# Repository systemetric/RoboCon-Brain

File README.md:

# RoboCon-Brain
Custom hardware and firmware for the RoboCon Brain, with PCB designs, embedded software and supporting files. Generations are documented through dedicated branches.

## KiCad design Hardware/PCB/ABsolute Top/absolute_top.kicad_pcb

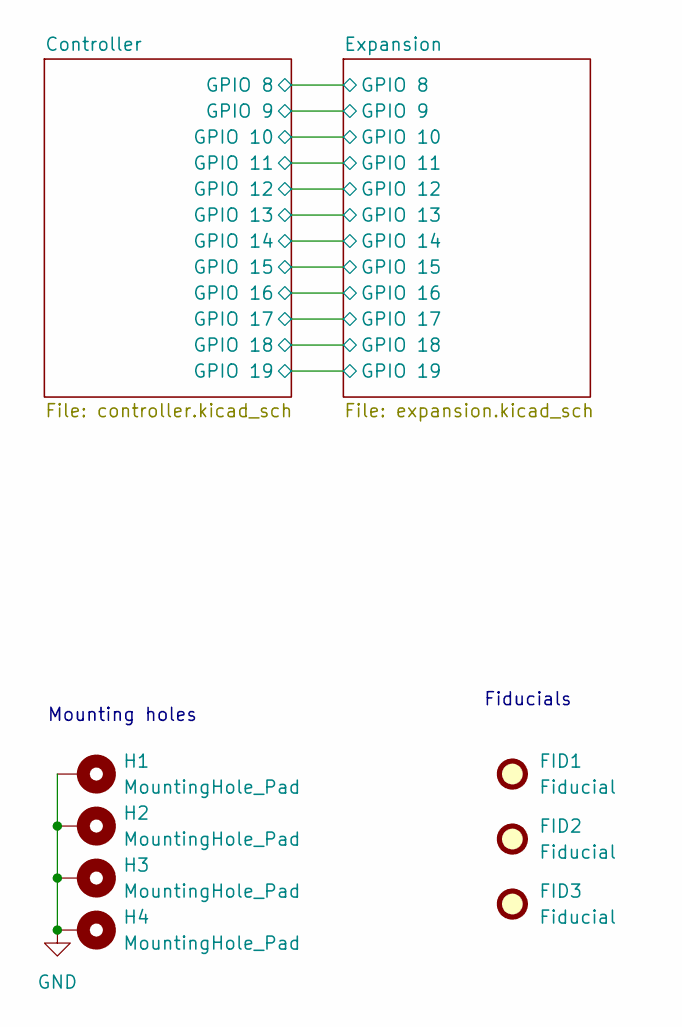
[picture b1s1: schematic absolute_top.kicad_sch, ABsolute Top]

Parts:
FID1, FID2, FID3: Fiducial; Fiducial_1mm_Mask2mm
H1, H2, H3, H4: MountingHole_Pad; MountingHole_3.2mm_M3_Pad_Via

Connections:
GND: H1.1 (1_1), H2.1 (1_1), H3.1 (1_1), H4.1 (1_1); also elsewhere on the board

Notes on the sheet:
Fiducials
Mounting holes

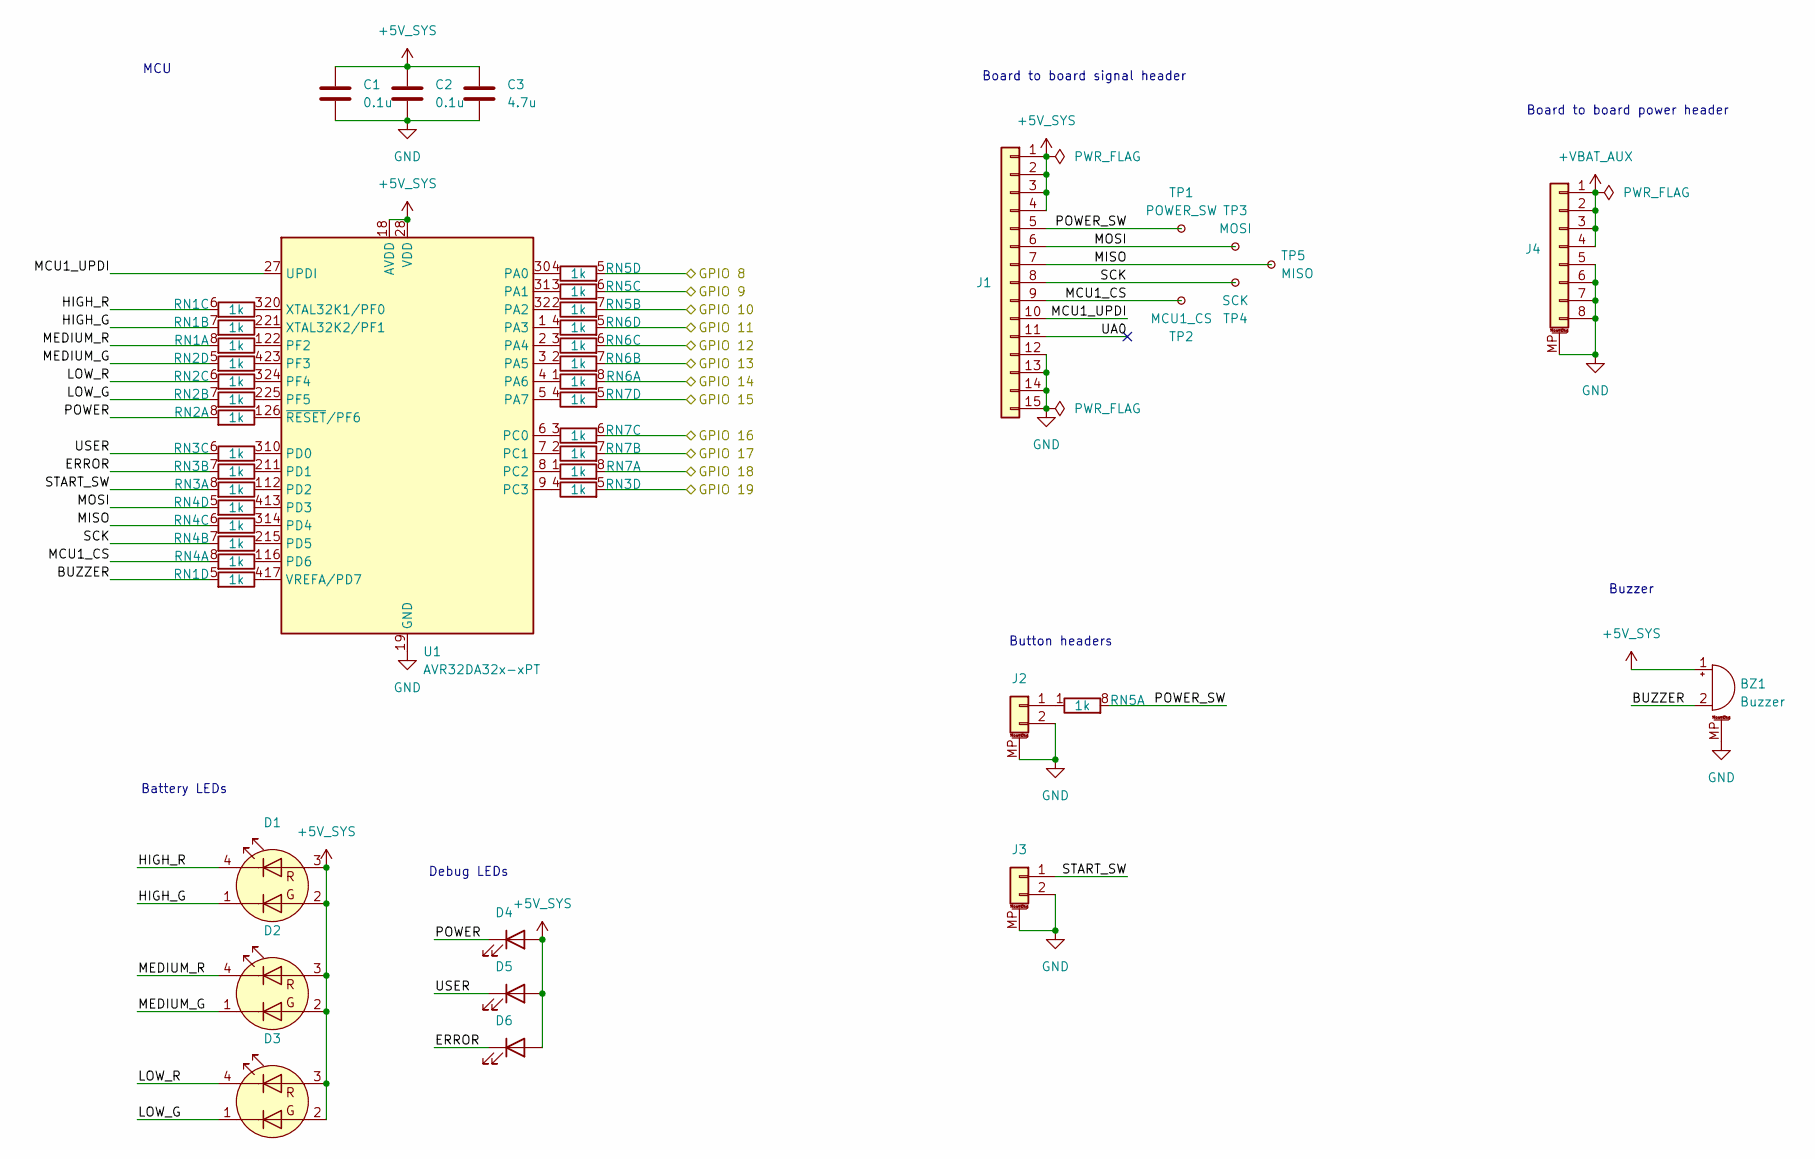
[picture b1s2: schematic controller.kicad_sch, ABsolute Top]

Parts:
BZ1: Buzzer; MagneticBuzzer_CUI_CMT-8504-100-SMT
C1, C2: 0.1u; C_0603_1608Metric
C3: 4.7u; C_0603_1608Metric
D1, D2, D3: LTST-C235KGKRKT; LED_LiteOn_LTST-C235; MPN LTST-C235KGKRKT
D4: LTST-C230KGKT; LED_LiteOn_LTST-C230; MPN LTST-C230KGKT
D5: LTST-C230TBKT; LED_LiteOn_LTST-C230; MPN LTST-C230TBKT
D6: LTST-C230KRKT; LED_LiteOn_LTST-C230; MPN LTST-C230KRKT
J1: Conn_01x15; PinSocket_1x15_P1.00mm_Vertical_SMD_Pin1Left
J2, J3: Conn_01x02_MountingPin; JST_PH_S2B-PH-SM4-TB_1x02-1MP_P2.00mm_Horizontal
J4: Conn_01x08_MountingPin; JST_PH_B8B-PH-SM4-TB_1x08-1MP_P2.00mm_Vertical
RN1, RN2, RN3, RN4, RN5, RN6, RN7: 1k; R_Array_Convex_4x0603
TP1: POWER_SW; TestPoint_Pad_D1.5mm
TP2: MCU1_CS; TestPoint_Pad_D1.5mm
TP3: MOSI; TestPoint_Pad_D1.5mm
TP4: SCK; TestPoint_Pad_D1.5mm
TP5: MISO; TestPoint_Pad_D1.5mm
U1: AVR32DA32x-xPT; TQFP-32_7x7mm_P0.8mm

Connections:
+5V_SYS: BZ1.1 (+), C1.1, C2.1, C3.1, D1.2 (A2), D1.3 (A1), D2.2 (A2), D2.3 (A1), D3.2 (A2), D3.3 (A1), D4.2 (A), D5.2 (A), D6.2 (A), J1.1, J1.2, J1.3, J1.4, U1.18 (AVDD), U1.28 (VDD)
+VBAT_AUX: J4.1, J4.2, J4.3, J4.4
/Controller/BUZZER: BZ1.2 (-), RN1.5 (R4.2)
/Controller/ERROR: D6.1 (K), RN3.7 (R2.2)
/Controller/GPIO 8: RN5.5 (R4.2); also elsewhere on the board
/Controller/GPIO 9: RN5.6 (R3.2); also elsewhere on the board
/Controller/GPIO 10: RN5.7 (R2.2); also elsewhere on the board
/Controller/GPIO 11: RN6.5 (R4.2); also elsewhere on the board
/Controller/GPIO 12: RN6.6 (R3.2); also elsewhere on the board
/Controller/GPIO 13: RN6.7 (R2.2); also elsewhere on the board
/Controller/GPIO 14: RN6.8 (R1.2); also elsewhere on the board
/Controller/GPIO 15: RN7.5 (R4.2); also elsewhere on the board
/Controller/GPIO 16: RN7.6 (R3.2); also elsewhere on the board
/Controller/GPIO 17: RN7.7 (R2.2); also elsewhere on the board
/Controller/GPIO 18: RN7.8 (R1.2); also elsewhere on the board
/Controller/GPIO 19: RN3.5 (R4.2); also elsewhere on the board
/Controller/HIGH_G: D1.1 (K2), RN1.7 (R2.2)
/Controller/HIGH_R: D1.4 (K1), RN1.6 (R3.2)
/Controller/LOW_G: D3.1 (K2), RN2.7 (R2.2)
/Controller/LOW_R: D3.4 (K1), RN2.6 (R3.2)
/Controller/MCU1_CS: J1.9, RN4.8 (R1.2), TP2.1 (1_1)
/Controller/MCU1_UPDI: J1.10, U1.27 (UPDI)
/Controller/MEDIUM_G: D2.1 (K2), RN2.5 (R4.2)
/Controller/MEDIUM_R: D2.4 (K1), RN1.8 (R1.2)
/Controller/MISO: J1.7, RN4.6 (R3.2), TP5.1 (1_1)
/Controller/MOSI: J1.6, RN4.5 (R4.2), TP3.1 (1_1)
/Controller/POWER: D4.1 (K), RN2.8 (R1.2)
/Controller/POWER_SW: J1.5, RN5.8 (R1.2), TP1.1 (1_1)
/Controller/SCK: J1.8, RN4.7 (R2.2), TP4.1 (1_1)
/Controller/START_SW: J3.1, RN3.8 (R1.2)
/Controller/UA0: J1.11
/Controller/USER: D5.1 (K), RN3.6 (R3.2)
GND: BZ1.MP (MountPin), C1.2, C2.2, C3.2, J1.12, J1.13, J1.14, J1.15, J2.2, J2.MP (MountPin), J3.2, J3.MP (MountPin), J4.5, J4.6, J4.7, J4.8, J4.MP (MountPin), U1.19 (GND), U1.29 (GND); also elsewhere on the board
unnamed: J2.1, RN5.1 (R1.1)
unnamed: RN1.1 (R1.1), U1.22 (PF2)
unnamed: RN1.2 (R2.1), U1.21 (XTAL32K2/PF1)
unnamed: RN1.3 (R3.1), U1.20 (XTAL32K1/PF0)
unnamed: RN1.4 (R4.1), U1.17 (VREFA/PD7)
unnamed: RN2.1 (R1.1), U1.26 (~RESET/PF6)
unnamed: RN2.2 (R2.1), U1.25 (PF5)
unnamed: RN2.3 (R3.1), U1.24 (PF4)
unnamed: RN2.4 (R4.1), U1.23 (PF3)
unnamed: RN3.1 (R1.1), U1.12 (PD2)
unnamed: RN3.2 (R2.1), U1.11 (PD1)
unnamed: RN3.3 (R3.1), U1.10 (PD0)
unnamed: RN3.4 (R4.1), U1.9 (PC3)
unnamed: RN4.1 (R1.1), U1.16 (PD6)
unnamed: RN4.2 (R2.1), U1.15 (PD5)
unnamed: RN4.3 (R3.1), U1.14 (PD4)
unnamed: RN4.4 (R4.1), U1.13 (PD3)
unnamed: RN5.2 (R2.1), U1.32 (PA2)
unnamed: RN5.3 (R3.1), U1.31 (PA1)
unnamed: RN5.4 (R4.1), U1.30 (PA0)
unnamed: RN6.1 (R1.1), U1.4 (PA6)
unnamed: RN6.2 (R2.1), U1.3 (PA5)
unnamed: RN6.3 (R3.1), U1.2 (PA4)
unnamed: RN6.4 (R4.1), U1.1 (PA3)
unnamed: RN7.1 (R1.1), U1.8 (PC2)
unnamed: RN7.2 (R2.1), U1.7 (PC1)
unnamed: RN7.3 (R3.1), U1.6 (PC0)
unnamed: RN7.4 (R4.1), U1.5 (PA7)

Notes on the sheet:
Battery LEDs
Board to board power header
Buzzer
Debug LEDs
Board to board signal header
Button headers
MCU

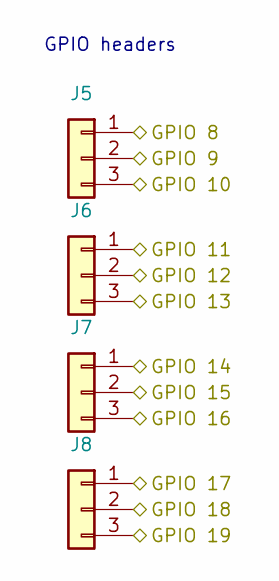
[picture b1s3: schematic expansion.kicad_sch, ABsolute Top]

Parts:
J5, J6, J7, J8: Conn_01x03; Harwin_M20-89003xx_1x03_P2.54mm_Horizontal

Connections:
/Controller/GPIO 8: J5.1; also elsewhere on the board
/Controller/GPIO 9: J5.2; also elsewhere on the board
/Controller/GPIO 10: J5.3; also elsewhere on the board
/Controller/GPIO 11: J6.1; also elsewhere on the board
/Controller/GPIO 12: J6.2; also elsewhere on the board
/Controller/GPIO 13: J6.3; also elsewhere on the board
/Controller/GPIO 14: J7.1; also elsewhere on the board
/Controller/GPIO 15: J7.2; also elsewhere on the board
/Controller/GPIO 16: J7.3; also elsewhere on the board
/Controller/GPIO 17: J8.1; also elsewhere on the board
/Controller/GPIO 18: J8.2; also elsewhere on the board
/Controller/GPIO 19: J8.3; also elsewhere on the board

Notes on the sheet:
GPIO headers

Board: 2 copper layers, 38 parts (0 on the bottom side), 60 nets, no tracks yet.

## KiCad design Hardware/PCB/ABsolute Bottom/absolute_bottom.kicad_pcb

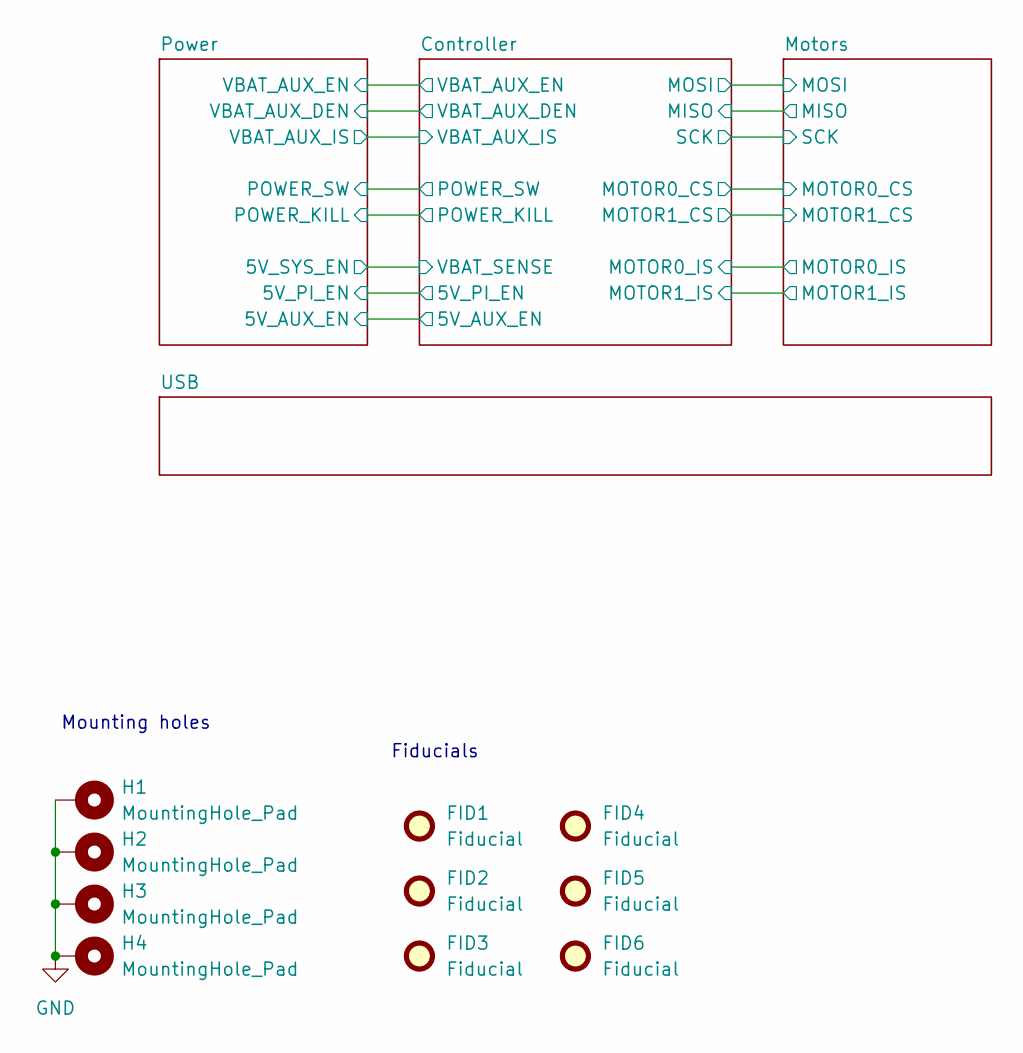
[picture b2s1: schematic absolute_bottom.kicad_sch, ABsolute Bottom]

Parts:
FID1, FID2, FID3, FID4, FID5, FID6: Fiducial; Fiducial_1mm_Mask2mm
H1, H2, H3, H4: MountingHole_Pad; MountingHole_3.2mm_M3_Pad_Via

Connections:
GND: H1.1 (1_1), H2.1 (1_1), H3.1 (1_1), H4.1 (1_1); also elsewhere on the board

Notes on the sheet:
Mounting holes
Fiducials

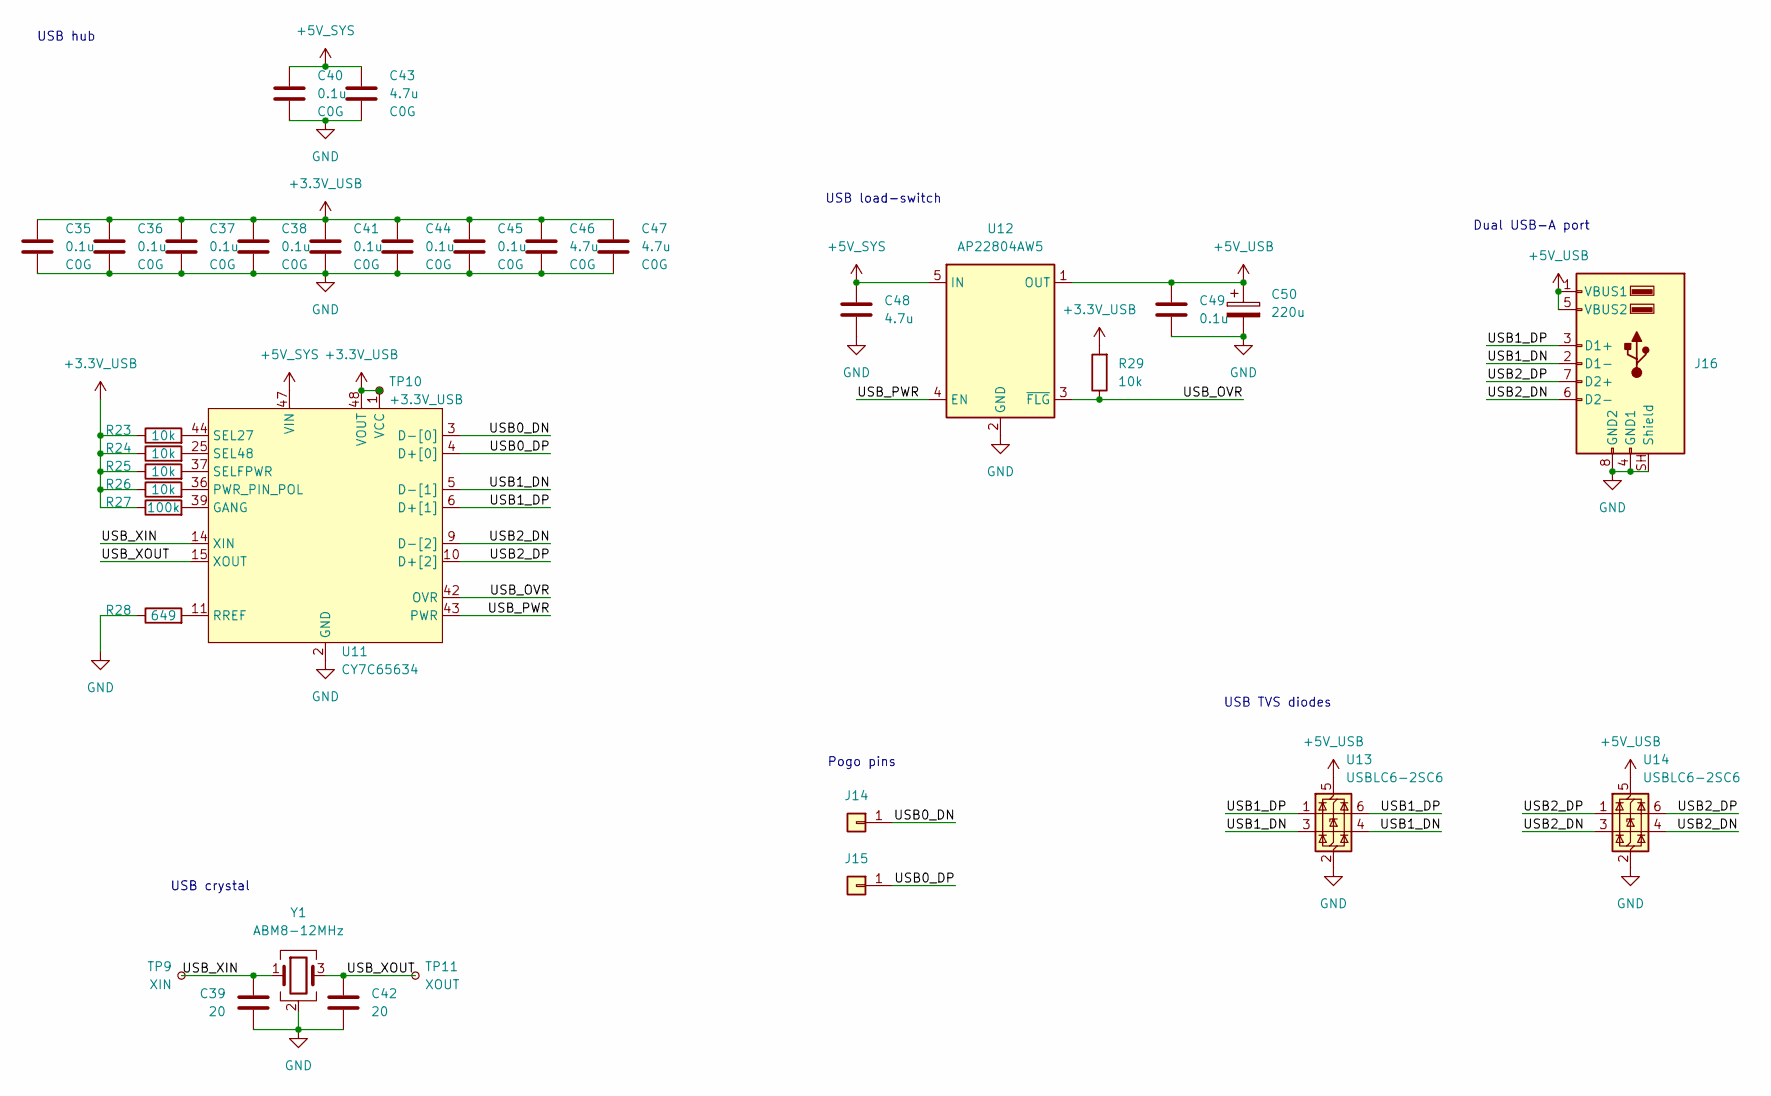
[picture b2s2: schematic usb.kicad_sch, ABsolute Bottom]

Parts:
C35, C36, C37, C38, C40, C41, C44, C45, C49: 0.1u; C_0603_1608Metric
C39, C42: 20; C_0603_1608Metric
C43, C46, C47, C48: 4.7u; C_0603_1608Metric
C50: 220u; CP_Elec_6.3x5.4_Nichicon
J14, J15: Conn_01x01; PinHeader_1x01_P2.54mm_Vertical
J16: USB_A_Stacked; USB_A_CUI_UJ2-ADH-TH_Horizontal_Stacked
R23, R24, R25, R26, R29: 10k; R_0603_1608Metric
R27: 100k; R_0603_1608Metric
R28: 649; R_0603_1608Metric
TP9: XIN; TestPoint_Pad_D1.5mm
TP10: +3.3V_USB; TestPoint_Pad_D1.5mm
TP11: XOUT; TestPoint_Pad_D1.5mm
U11: CY7C65634; TQFP-48_7x7mm_P0.5mm; MPN CY7C65634-48AXC
U12: AP22804AW5; SOT-23-5; MPN AP22804AW5-7
U13, U14: USBLC6-2SC6; SOT-23-6; MPN USBLC6-2SC6
Y1: ABM8-12MHz; Crystal_SMD_Abracon_ABM8AIG-4Pin_3.2x2.5mm; MPN ABM8-12.000MHZ-12-B1U-T

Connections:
+3.3V_USB: C35.1, C36.1, C37.1, C38.1, C41.1, C44.1, C45.1, C46.1, C47.1, R23.1, R24.1, R25.1, R26.1, R27.1, R29.2, TP10.1 (1_1), U11.1 (VCC), U11.7 (VCC), U11.12 (VCC), U11.16 (VCC), U11.34 (VCC), U11.38 (VCC), U11.48 (VOUT)
+5V_SYS: C40.1, C43.1, C48.1, U11.47 (VIN), U12.5 (IN); also elsewhere on the board
+5V_USB: C49.1, C50.1, J16.1 (VBUS1), J16.5 (VBUS2), U12.1 (OUT), U13.5 (VBUS), U14.5 (VBUS)
/USB/USB0_DN: J14.1 (Pin_1_1), U11.3 (D-[0])
/USB/USB0_DP: J15.1 (Pin_1_1), U11.4 (D+[0])
/USB/USB1_DN: J16.2 (D1-), U11.5 (D-[1]), U13.3 (I/O2), U13.4 (I/O2)
/USB/USB1_DP: J16.3 (D1+), U11.6 (D+[1]), U13.1 (I/O1), U13.6 (I/O1)
/USB/USB2_DN: J16.6 (D2-), U11.9 (D-[2]), U14.3 (I/O2), U14.4 (I/O2)
/USB/USB2_DP: J16.7 (D2+), U11.10 (D+[2]), U14.1 (I/O1), U14.6 (I/O1)
/USB/USB_OVR: R29.1, U11.42 (OVR), U12.3 (~FLG)
/USB/USB_PWR: U11.43 (PWR), U12.4 (EN)
/USB/USB_XIN: C39.1, TP9.1 (1_1), U11.14 (XIN), Y1.1
/USB/USB_XOUT: C42.1, TP11.1 (1_1), U11.15 (XOUT), Y1.3
GND: C35.2, C36.2, C37.2, C38.2, C39.2, C40.2, C41.2, C42.2, C43.2, C44.2, C45.2, C46.2, C47.2, C48.2, C49.2, C50.2, J16.4 (GND1), J16.8 (GND2), J16.SH (Shield), R28.1, U11.2 (GND), U11.8 (GND), U11.13 (GND), U11.20 (GND), U12.2 (GND), U13.2 (GND), U14.2 (GND), Y1.2 (G), Y1.4 (G); also elsewhere on the board
unnamed: R27.2, U11.39 (GANG)
unnamed: R26.2, U11.36 (PWR_PIN_POL)
unnamed: R28.2, U11.11 (RREF)
unnamed: R23.2, U11.44 (SEL27)
unnamed: R24.2, U11.25 (SEL48)
unnamed: R25.2, U11.37 (SELFPWR)

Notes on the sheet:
USB hub
Pogo pins
USB crystal
USB load-switch
Dual USB-A port
USB TVS diodes

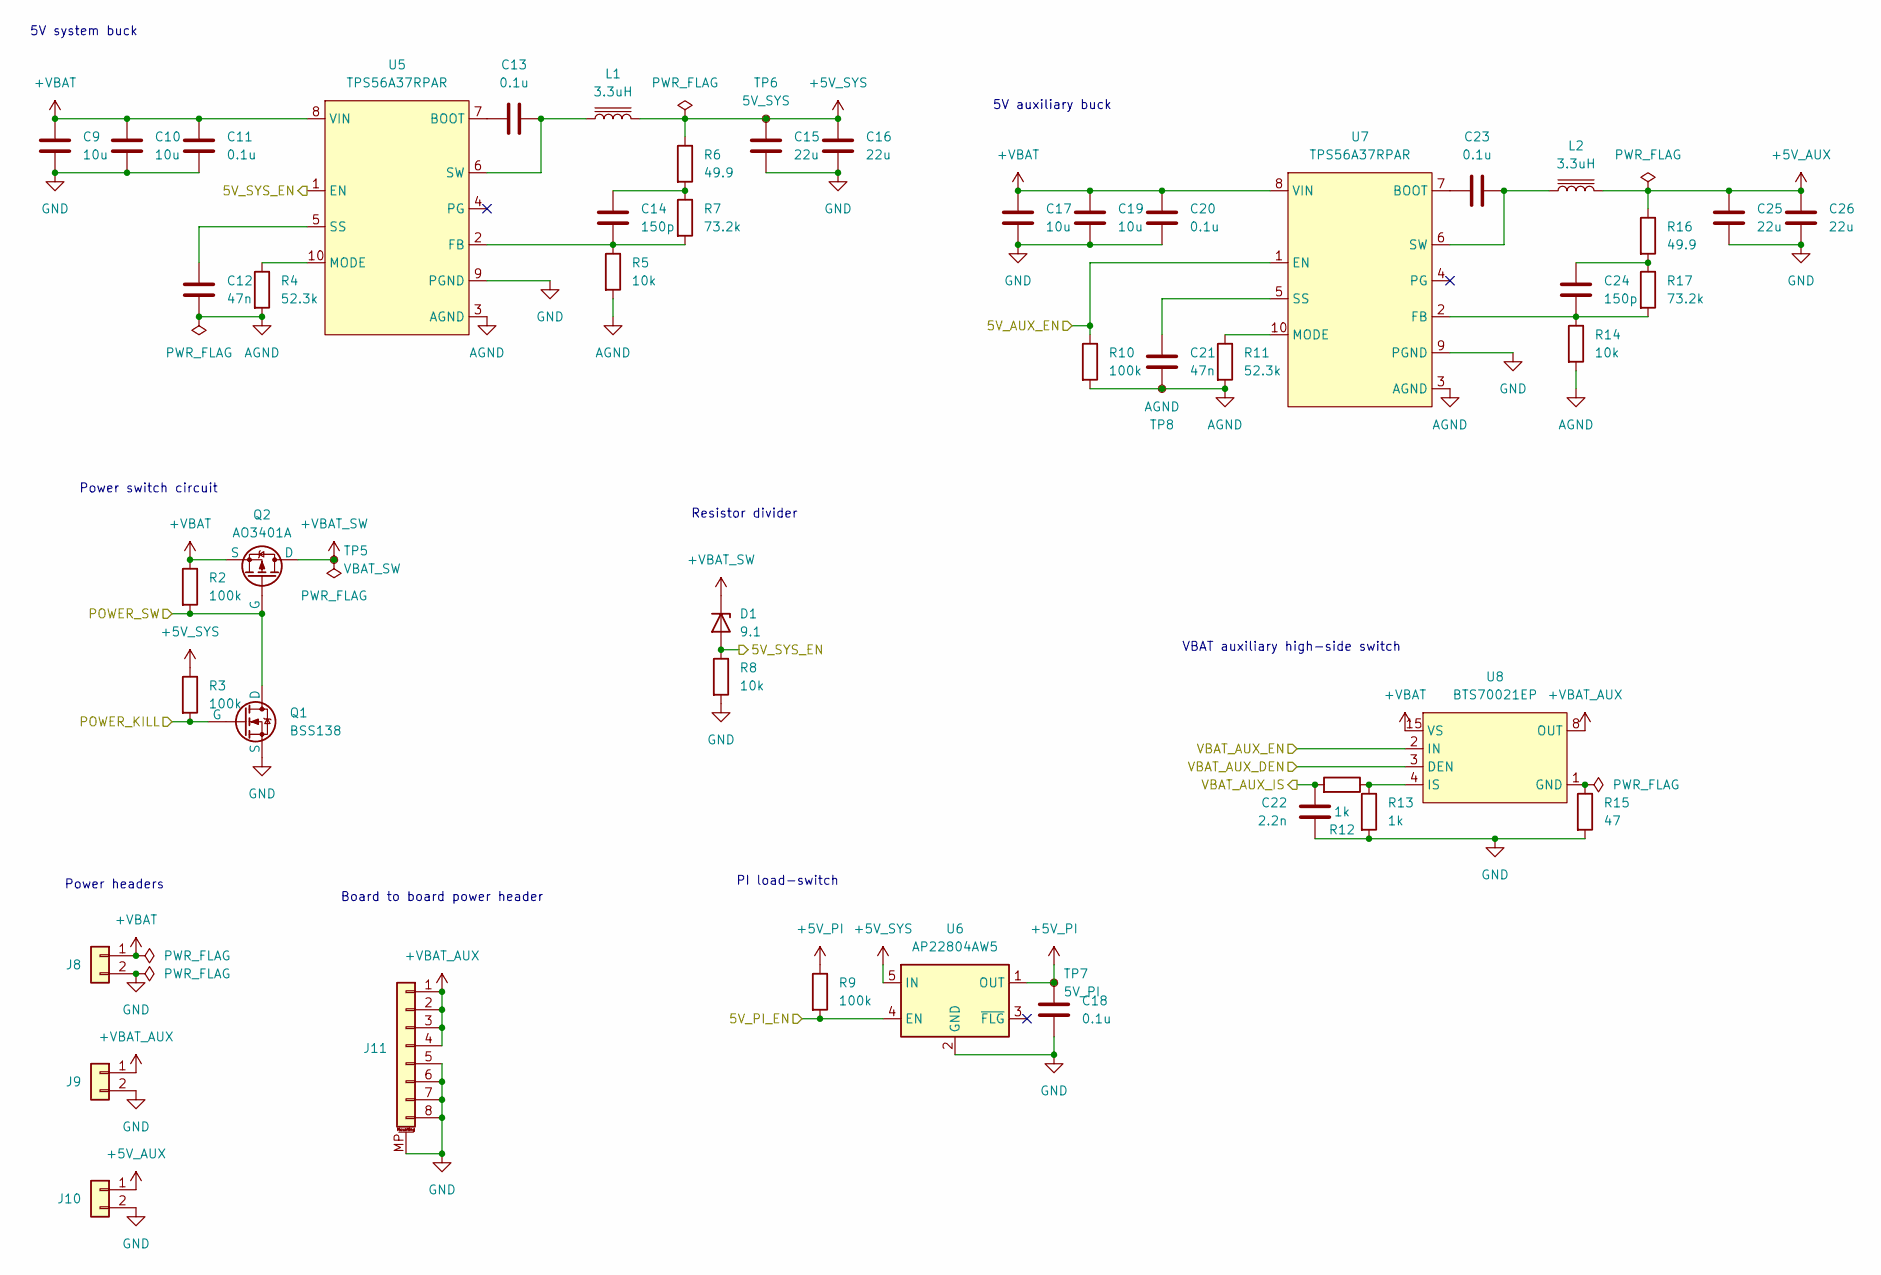
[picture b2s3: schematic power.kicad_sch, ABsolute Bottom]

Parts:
C9, C10, C17, C19: 10u; C_0603_1608Metric
C11, C13, C18, C20, C23: 0.1u; C_0603_1608Metric
C12, C21: 47n; C_0603_1608Metric
C14, C24: 150p; C_0603_1608Metric
C15, C16, C25, C26: 22u; C_1210_3225Metric
C22: 2.2n; C_0603_1608Metric
D1: 9.1; D_SOD-123
J8: Conn_01x02; AMASS_XT60PW-M_1x02_P7.20mm_Horizontal
J9, J10: Conn_01x02; PhoenixContact_MC_1,5_2-G-3.5_1x02_P3.50mm_Horizontal
J11: Conn_01x08_MountingPin; JST_PH_B8B-PH-SM4-TB_1x08-1MP_P2.00mm_Vertical
L1, L2: 3.3uH; L_Wuerth_XHMI-6060; MPN 744393445033
Q1: BSS138; SOT-23-3; MPN BSS138
Q2: AO3401A; SOT-23-3; MPN AO3401A
R2, R3, R9, R10: 100k; R_0603_1608Metric
R4, R11: 52.3k; R_0603_1608Metric
R5, R8, R14: 10k; R_0603_1608Metric
R6, R16: 49.9; R_0603_1608Metric
R7, R17: 73.2k; R_0603_1608Metric
R12, R13: 1k; R_0603_1608Metric
R15: 47; R_0603_1608Metric
TP5: VBAT_SW; TestPoint_Pad_D1.5mm
TP6: 5V_SYS; TestPoint_Pad_D1.5mm
TP7: 5V_PI; TestPoint_Pad_D1.5mm
TP8: AGND; TestPoint_Pad_D1.5mm
U5, U7: TPS56A37RPAR; RPA0010A; MPN TPS56A37RPAR
U6: AP22804AW5; SOT-23-5; MPN AP22804AW5-7
U8: BTS70021EP; Infineon_PG-TSDSO-14-22; MPN BTS70021EPPXUMA1

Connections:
+5V_AUX: C25.2, C26.2, J10.1, L2.2, R16.1; also elsewhere on the board
+5V_PI: C18.2, R9.1, TP7.1 (1_1), U6.1 (OUT); also elsewhere on the board
+5V_SYS: C15.2, C16.2, L1.2, R3.1, R6.1, TP6.1 (1_1), U6.5 (IN); also elsewhere on the board
+VBAT: C9.2, C10.2, C11.2, C17.2, C19.2, C20.2, J8.1, Q2.3 (S), R2.1, U5.8 (VIN), U7.8 (VIN), U8.15 (VS); also elsewhere on the board
+VBAT_AUX: J9.1, J11.1, J11.2, J11.3, J11.4, U8.8 (OUT), U8.9 (OUT), U8.10 (OUT), U8.12 (OUT), U8.13 (OUT), U8.14 (OUT)
+VBAT_SW: D1.1 (K), Q2.1 (D), TP5.1 (1_1)
/Controller/5V_AUX_EN: R10.1, U7.1 (EN); also elsewhere on the board
/Controller/5V_PI_EN: R9.2, U6.4 (EN); also elsewhere on the board
/Controller/POWER_KILL: Q1.2 (G), R3.2; also elsewhere on the board
/Controller/POWER_SW: Q1.1 (D), Q2.2 (G), R2.2; also elsewhere on the board
/Controller/VBAT_AUX_DEN: U8.3 (DEN); also elsewhere on the board
/Controller/VBAT_AUX_EN: U8.2 (IN); also elsewhere on the board
/Controller/VBAT_AUX_IS: C22.2, R12.2; also elsewhere on the board
/Controller/VBAT_SENSE: D1.2 (A), R8.1, U5.1 (EN); also elsewhere on the board
AGND: C12.1, C21.1, R4.2, R5.2, R10.2, R11.2, R14.2, TP8.1 (1_1), U5.3 (AGND), U7.3 (AGND)
GND: C9.1, C10.1, C11.1, C15.1, C16.1, C17.1, C18.1, C19.1, C20.1, C22.1, C25.1, C26.1, J8.2, J9.2, J10.2, J11.5, J11.6, J11.7, J11.8, J11.MP (MountPin), Q1.3 (S), R8.2, R13.2, R15.2, U5.9 (PGND), U6.2 (GND), U7.9 (PGND); also elsewhere on the board
unnamed: C14.2, R6.2, R7.1
unnamed: C24.2, R16.2, R17.1
unnamed: C13.1, U5.7 (BOOT)
unnamed: C14.1, R5.1, R7.2, U5.2 (FB)
unnamed: R4.1, U5.10 (MODE)
unnamed: C12.2, U5.5 (SS)
unnamed: C13.2, L1.1, U5.6 (SW)
unnamed: C23.1, U7.7 (BOOT)
unnamed: C24.1, R14.1, R17.2, U7.2 (FB)
unnamed: R11.1, U7.10 (MODE)
unnamed: C21.2, U7.5 (SS)
unnamed: C23.2, L2.1, U7.6 (SW)
unnamed: R15.1, U8.1 (GND)
unnamed: R12.1, R13.1, U8.4 (IS)

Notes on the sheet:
Power headers
Board to board power header
Power switch circuit
Resistor divider
5V auxiliary buck
PI load-switch
VBAT auxiliary high-side switch
5V system buck

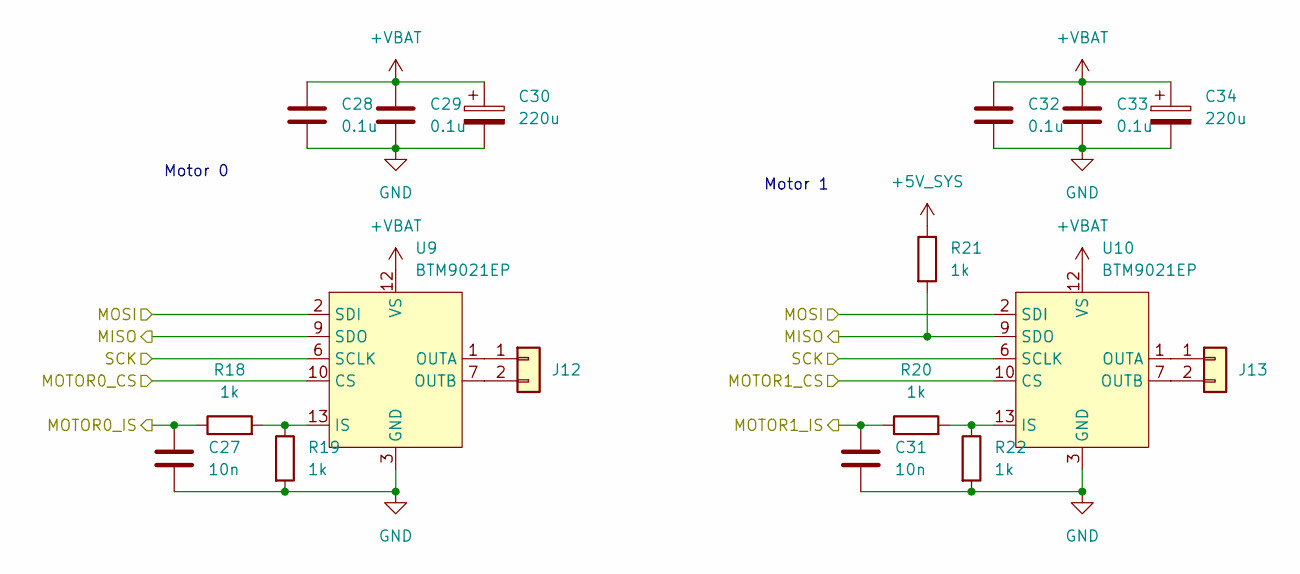
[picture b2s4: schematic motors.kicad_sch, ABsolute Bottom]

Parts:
C27, C31: 10n; C_0603_1608Metric
C28, C29, C32, C33: 0.1u; C_0603_1608Metric
C30, C34: 220u; CP_Elec_6.3x5.4_Nichicon
J12, J13: Conn_01x02; PhoenixContact_MC_1,5_2-G-3.5_1x02_P3.50mm_Horizontal
R18, R19, R20, R21, R22: 1k; R_0603_1608Metric
U9, U10: BTM9021EP; Infineon_PG-TSDSO-14-22; MPN BTM9021EPXUMA1

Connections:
+5V_SYS: R21.1; also elsewhere on the board
+VBAT: C28.1, C29.1, C30.1, C32.1, C33.1, C34.1, U9.11 (VS), U9.12 (VS), U10.11 (VS), U10.12 (VS); also elsewhere on the board
/Controller/MISO: R21.2, U9.9 (SDO), U10.9 (SDO); also elsewhere on the board
/Controller/MOSI: U9.2 (SDI), U10.2 (SDI); also elsewhere on the board
/Controller/MOTOR0_CS: U9.10 (CS); also elsewhere on the board
/Controller/MOTOR0_IS: C27.1, R18.1; also elsewhere on the board
/Controller/MOTOR1_CS: U10.10 (CS); also elsewhere on the board
/Controller/MOTOR1_IS: C31.1, R20.1; also elsewhere on the board
/Controller/SCK: U9.6 (SCLK), U10.6 (SCLK); also elsewhere on the board
GND: C27.2, C28.2, C29.2, C30.2, C31.2, C32.2, C33.2, C34.2, R19.2, R22.2, U9.3 (GND), U9.4 (GND), U9.5 (GND), U9.15 (GND), U10.3 (GND), U10.4 (GND), U10.5 (GND), U10.15 (GND); also elsewhere on the board
unnamed: J12.1, U9.1 (OUTA), U9.14 (OUTA)
unnamed: J12.2, U9.7 (OUTB), U9.8 (OUTB)
unnamed: J13.1, U10.1 (OUTA), U10.14 (OUTA)
unnamed: J13.2, U10.7 (OUTB), U10.8 (OUTB)
unnamed: R18.2, R19.1, U9.13 (IS)
unnamed: R20.2, R22.1, U10.13 (IS)

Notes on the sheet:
Motor 1
Motor 0

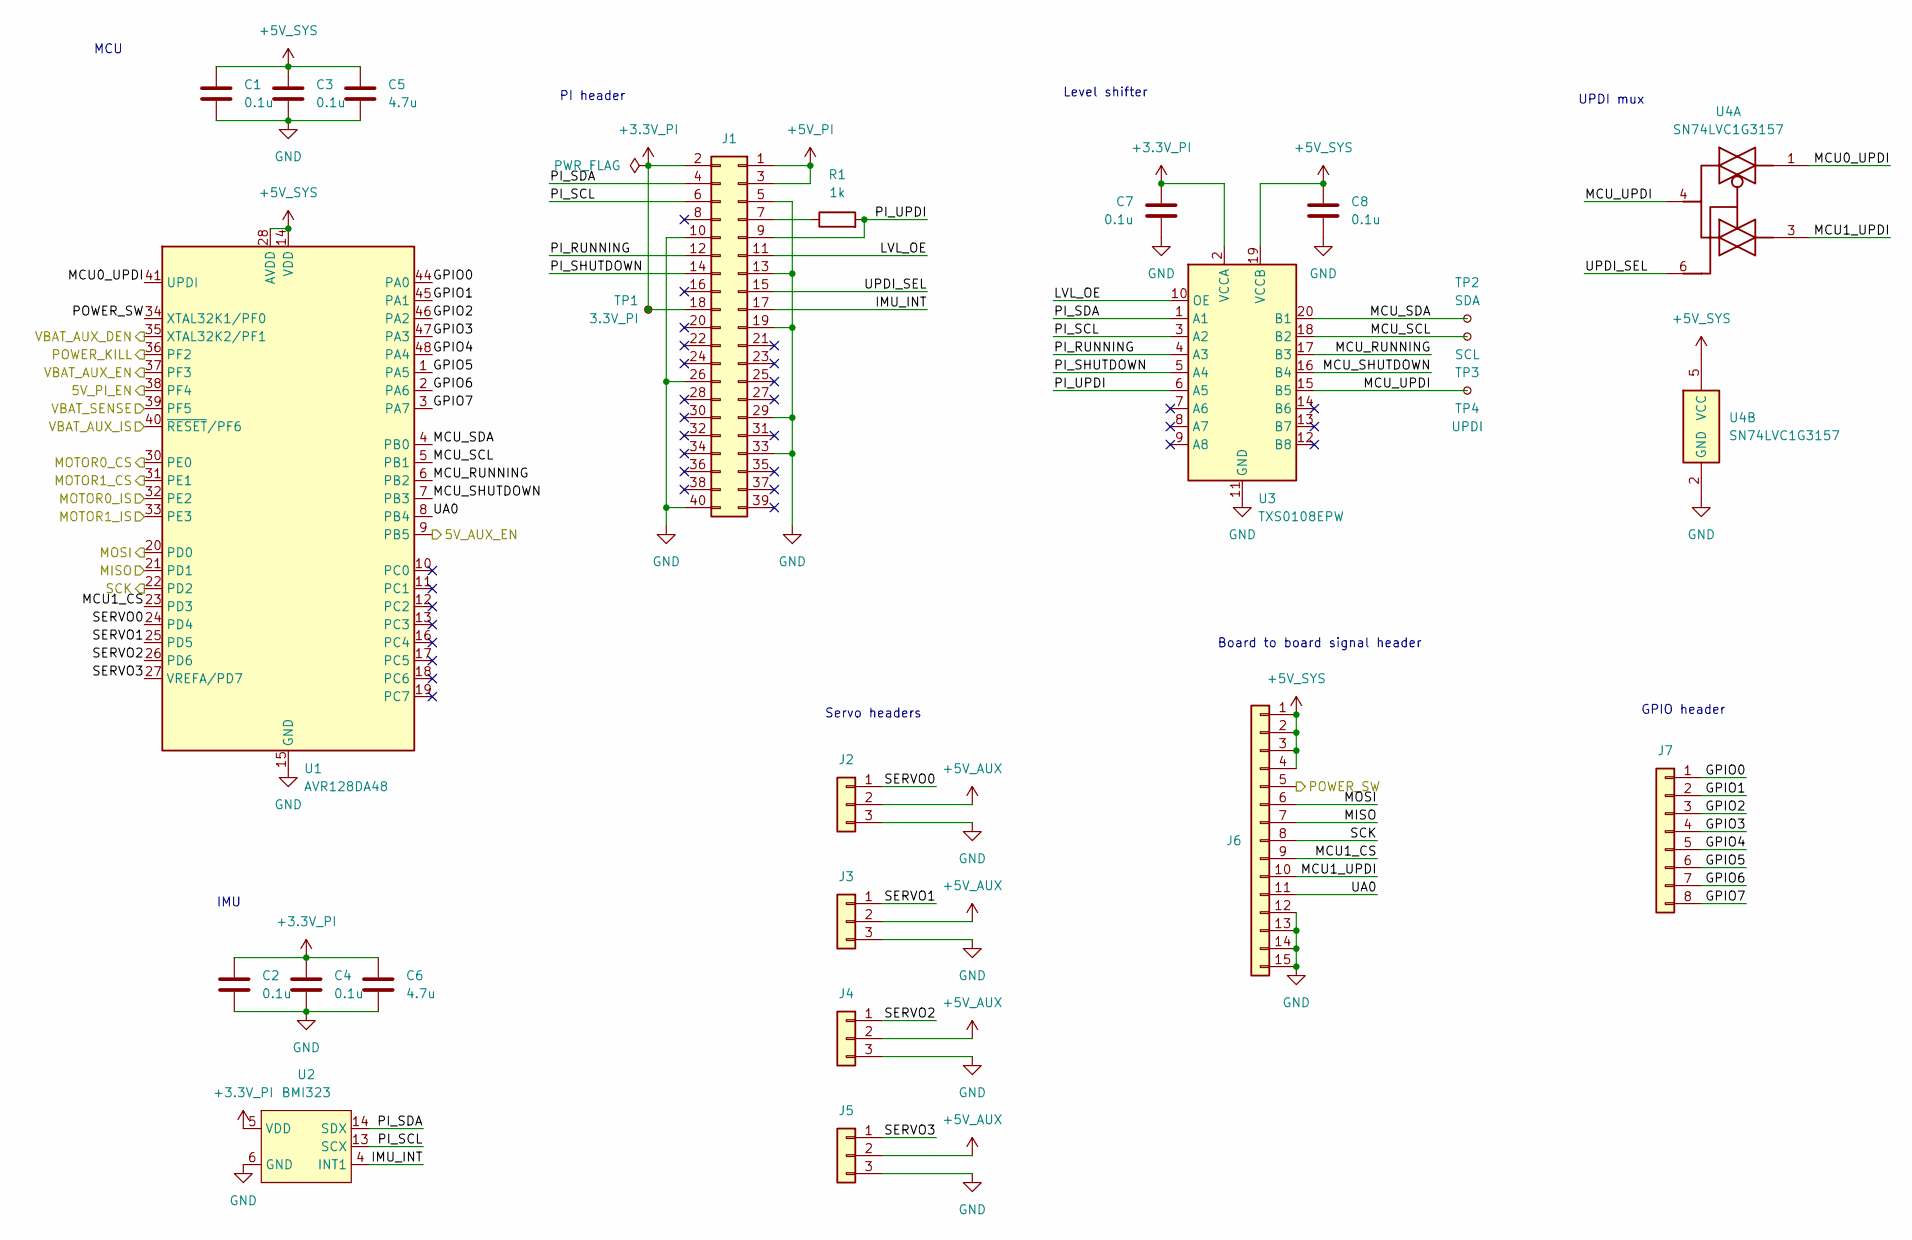
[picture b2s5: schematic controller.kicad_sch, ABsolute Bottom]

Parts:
C1, C2, C3, C4, C7, C8: 0.1u; C_0603_1608Metric
C5, C6: 4.7u; C_0603_1608Metric
J1: Conn_02x20_Odd_Even; PinSocket_2x20_P2.54mm_Vertical_SMD
J2, J3, J4, J5: Conn_01x03; PinHeader_1x03_P2.54mm_Horizontal
J6: Conn_01x15; PinSocket_1x15_P1.00mm_Vertical_SMD_Pin1Left
J7: Conn_01x08; PhoenixContact_MC_1,5_8-G-3.5_1x08_P3.50mm_Horizontal
R1: 1k; R_0603_1608Metric
TP1: 3.3V_PI; TestPoint_Pad_D1.5mm
TP2: SDA; TestPoint_Pad_D1.5mm
TP3: SCL; TestPoint_Pad_D1.5mm
TP4: UPDI; TestPoint_Pad_D1.5mm
U1: AVR128DA48; TQFP-48_7x7mm_P0.5mm
U2: BMI323; Bosch_LGA-14_3x2.5mm_P0.5mm; MPN BMI323
U3: TXS0108EPW; TSSOP-20_4.4x6.5mm_P0.65mm
U4: SN74LVC1G3157; SOT-363_SC-70-6; MPN SN74LVC1G3157DCKR

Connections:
+3.3V_PI: C2.1, C4.1, C6.1, C7.2, J1.2, J1.18, TP1.1 (1_1), U2.5 (VDD), U2.8 (VDD), U3.2 (VCCA)
+5V_AUX: J2.2, J3.2, J4.2, J5.2; also elsewhere on the board
+5V_PI: J1.1, J1.3; also elsewhere on the board
+5V_SYS: C1.1, C3.1, C5.1, C8.2, J6.1, J6.2, J6.3, J6.4, U1.14 (VDD), U1.28 (AVDD), U1.42 (VDD), U3.19 (VCCB), U4.5 (VCC); also elsewhere on the board
/Controller/5V_AUX_EN: U1.9 (PB5); also elsewhere on the board
/Controller/5V_PI_EN: U1.38 (PF4); also elsewhere on the board
/Controller/GPIO0: J7.1, U1.44 (PA0)
/Controller/GPIO1: J7.2, U1.45 (PA1)
/Controller/GPIO2: J7.3, U1.46 (PA2)
/Controller/GPIO3: J7.4, U1.47 (PA3)
/Controller/GPIO4: J7.5, U1.48 (PA4)
/Controller/GPIO5: J7.6, U1.1 (PA5)
/Controller/GPIO6: J7.7, U1.2 (PA6)
/Controller/GPIO7: J7.8, U1.3 (PA7)
/Controller/IMU_INT: J1.17, U2.4 (INT1)
/Controller/LVL_OE: J1.11, U3.10 (OE)
/Controller/MCU0_UPDI: U1.41 (UPDI), U4.1
/Controller/MCU1_CS: J6.9, U1.23 (PD3)
/Controller/MCU1_UPDI: J6.10, U4.3
/Controller/MCU_RUNNING: U1.6 (PB2), U3.17 (B3)
/Controller/MCU_SCL: TP3.1 (1_1), U1.5 (PB1), U3.18 (B2)
/Controller/MCU_SDA: TP2.1 (1_1), U1.4 (PB0), U3.20 (B1)
/Controller/MCU_SHUTDOWN: U1.7 (PB3), U3.16 (B4)
/Controller/MCU_UPDI: TP4.1 (1_1), U3.15 (B5), U4.4
/Controller/MISO: J6.7, U1.21 (PD1); also elsewhere on the board
/Controller/MOSI: J6.6, U1.20 (PD0); also elsewhere on the board
/Controller/MOTOR0_CS: U1.30 (PE0); also elsewhere on the board
/Controller/MOTOR0_IS: U1.32 (PE2); also elsewhere on the board
/Controller/MOTOR1_CS: U1.31 (PE1); also elsewhere on the board
/Controller/MOTOR1_IS: U1.33 (PE3); also elsewhere on the board
/Controller/PI_RUNNING: J1.12, U3.4 (A3)
/Controller/PI_SCL: J1.6, U2.13 (SCX), U3.3 (A2)
/Controller/PI_SDA: J1.4, U2.14 (SDX), U3.1 (A1)
/Controller/PI_SHUTDOWN: J1.14, U3.5 (A4)
/Controller/PI_UPDI: J1.9, R1.2, U3.6 (A5)
/Controller/POWER_KILL: U1.36 (PF2); also elsewhere on the board
/Controller/POWER_SW: J6.5, U1.34 (XTAL32K1/PF0); also elsewhere on the board
/Controller/SCK: J6.8, U1.22 (PD2); also elsewhere on the board
/Controller/SERVO0: J2.1, U1.24 (PD4)
/Controller/SERVO1: J3.1, U1.25 (PD5)
/Controller/SERVO2: J4.1, U1.26 (PD6)
/Controller/SERVO3: J5.1, U1.27 (VREFA/PD7)
/Controller/UA0: J6.11, U1.8 (PB4)
/Controller/UPDI_SEL: J1.15, U4.6
/Controller/VBAT_AUX_DEN: U1.35 (XTAL32K2/PF1); also elsewhere on the board
/Controller/VBAT_AUX_EN: U1.37 (PF3); also elsewhere on the board
/Controller/VBAT_AUX_IS: U1.40 (~RESET/PF6); also elsewhere on the board
/Controller/VBAT_SENSE: U1.39 (PF5); also elsewhere on the board
GND: C1.2, C2.2, C3.2, C4.2, C5.2, C6.2, C7.1, C8.1, J1.5, J1.10, J1.13, J1.19, J1.26, J1.29, J1.33, J1.40, J2.3, J3.3, J4.3, J5.3, J6.12, J6.13, J6.14, J6.15, U1.15 (GND), U1.29 (GND), U1.43 (GND), U2.1 (SA0), U2.6 (GND), U2.7 (GND), U3.11 (GND), U4.2 (GND); also elsewhere on the board
unnamed: J1.7, R1.1

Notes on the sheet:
Board to board signal header
IMU
GPIO header
PI header
Level shifter
MCU
UPDI mux
Servo headers

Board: 2 copper layers, 136 parts (0 on the bottom side), 92 nets, no tracks yet.
